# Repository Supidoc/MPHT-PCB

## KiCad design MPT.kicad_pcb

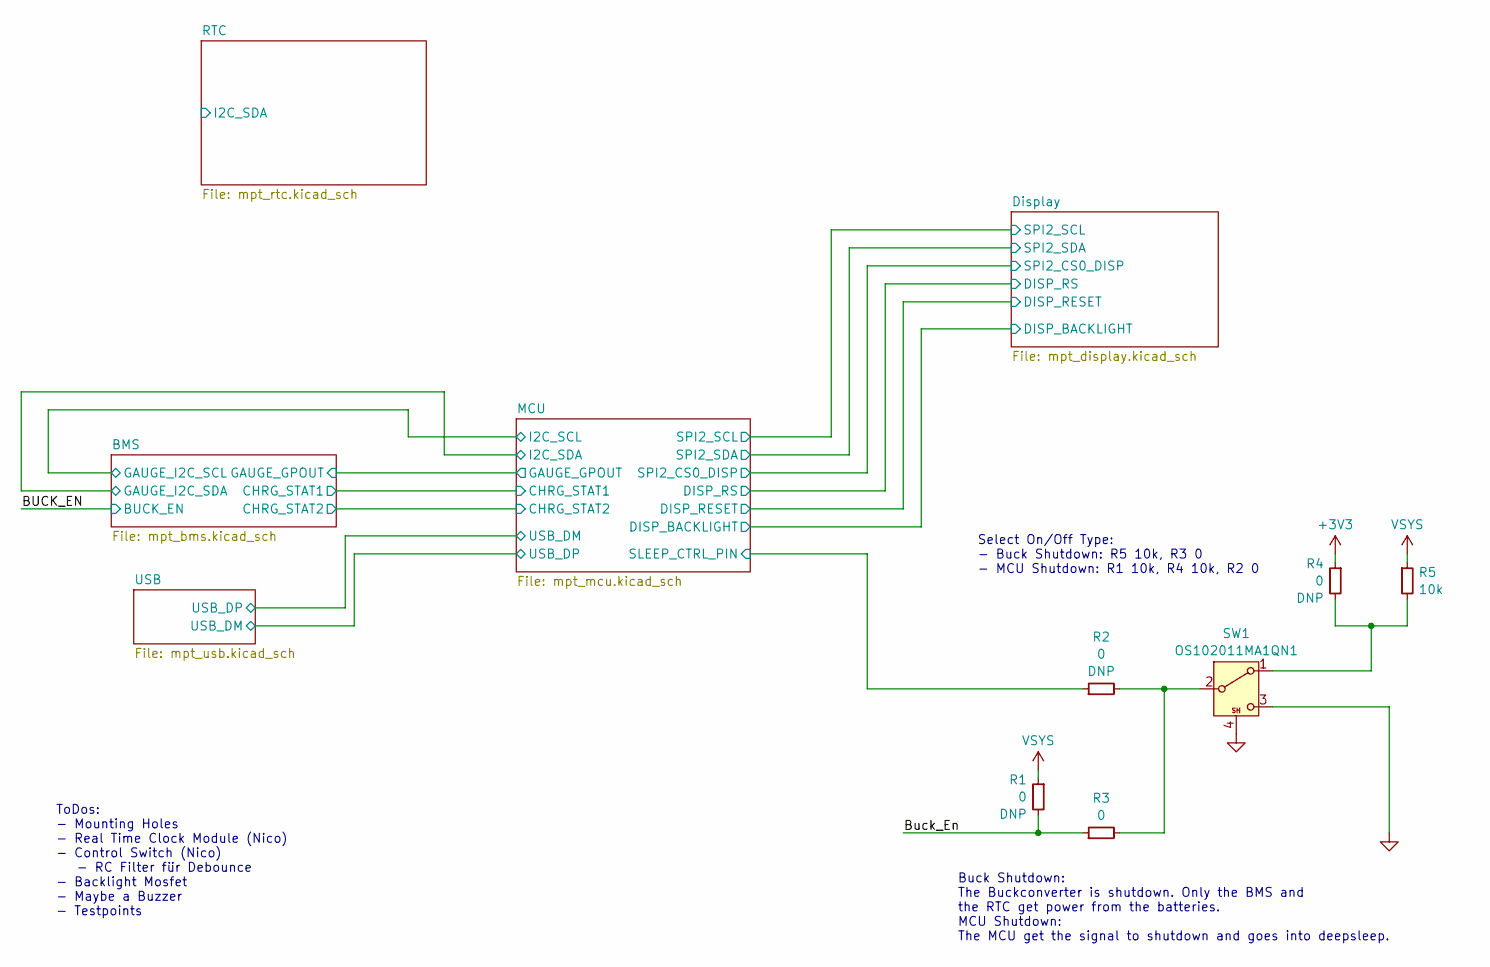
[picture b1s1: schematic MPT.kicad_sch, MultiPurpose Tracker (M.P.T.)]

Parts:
R1, R2, R4: 0; R_0603_DNP
R3: 0; R_0603; Rating 100mW; MFR# RC0603JR-070RL
R5: 10k; R_0603; Rating 125mW, 1%; MFR# RC0603FR-0710KL
SW1: OS102011MA1QN1; OS102011MA1QN1_CNK; Rating 100MA 12V Non-shorting; MFR# OS102011MA1QN1

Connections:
+3V3: R4.1; also elsewhere on the board
/Buck_En: R1.2, R3.1
/MCU/SLEEP_CTRL_PIN: R2.1; also elsewhere on the board
GND: SW1.3 (C), SW1.4 (SH); also elsewhere on the board
unnamed: R4.2, R5.2, SW1.1 (A)
unnamed: R2.2, R3.2, SW1.2 (B)
VSYS: R1.1, R5.1; also elsewhere on the board

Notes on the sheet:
Select On/Off Type: - Buck Shutdown: R5 10k, R3 0 - MCU Shutdown: R1 10k, R4 10k, R2 0
Buck Shutdown: The Buckconverter is shutdown. Only the BMS and the RTC get power from the batteries. MCU Shutdown: The MCU get the signal to shutdown and goes into deepsleep.
ToDos: - Mounting Holes - Real Time Clock Module (Nico) - Control Switch (Nico) - RC Filter für Debounce - Backlight Mosfet - Maybe a Buzzer - Testpoints

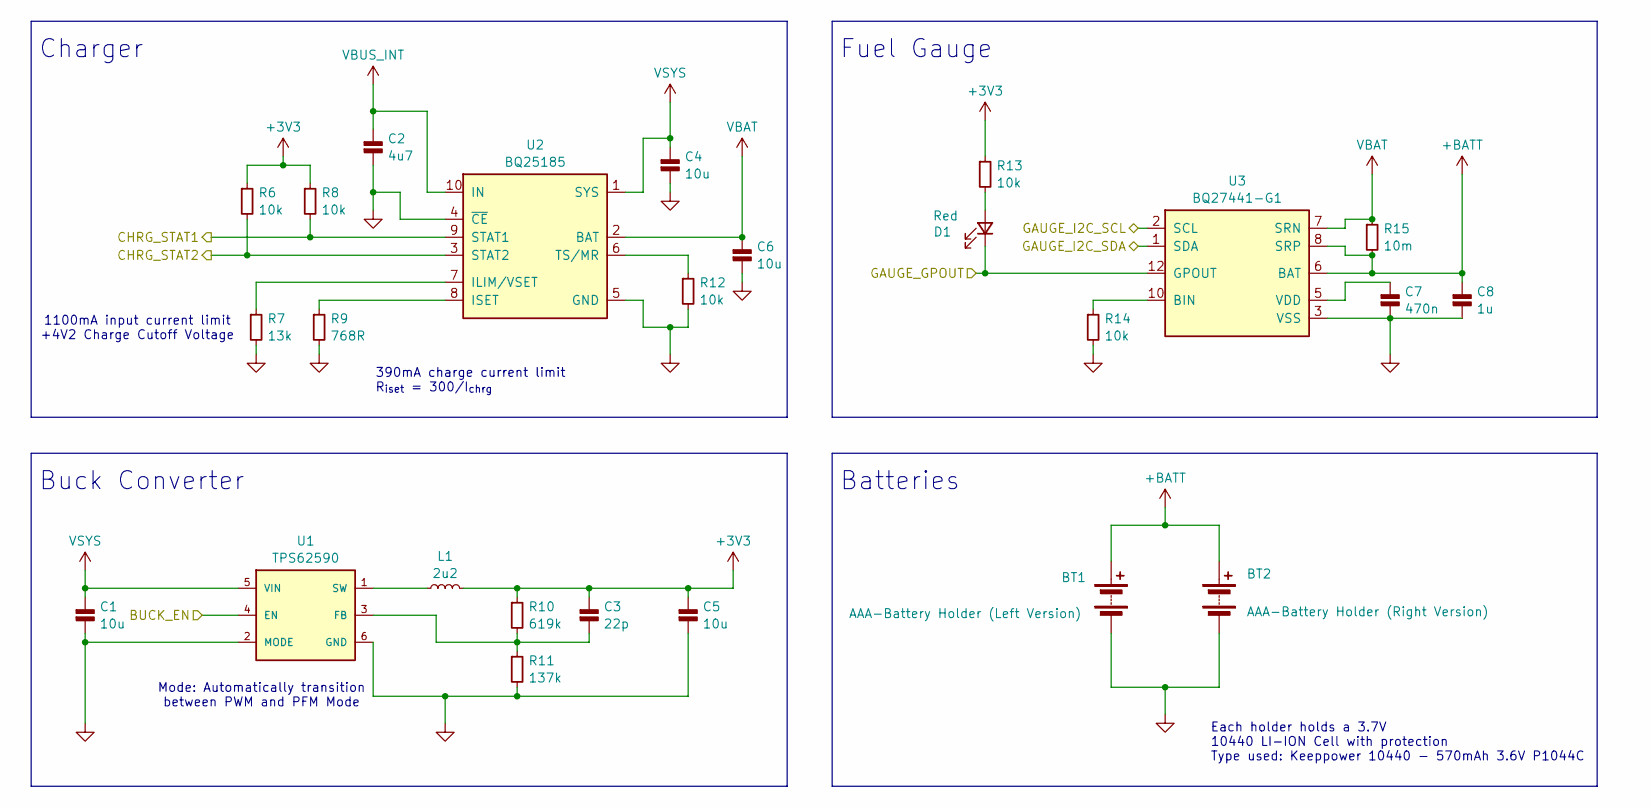
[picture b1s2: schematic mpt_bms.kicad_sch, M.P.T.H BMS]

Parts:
BT1: AAA-Battery Holder (Left Version); battery_holder_aaa_right_angle_left; MFR# 2466
BT2: AAA-Battery Holder (Right Version); battery_holder_aaa_right_angle_right; MFR# 2466
C1, C4, C5, C6: 10u; C_0603; Rating 10V 20%; MFR# CC0603MRX5R6BB106
C2: 4u7; C_0805; Rating 25V 10%; MFR# CC0805KKX7R8BB475
C3: 22p; C_0603; Rating 100V 5%; MFR# CC0603JPNPO0BN220
C7: 470n; C_0603; Rating 16V 10%; MFR# CC0603KRX7R7BB474
C8: 1u; C_0603; Rating 50V 10%; MFR# CC0603KRX7R9BB105
D1: Red; LED_0805_Right_Angle; Rating 20mA; MFR# LTST-S220KRKT
L1: 2u2; L_3.2mmx2.5mm; Rating 4A, 20%, 61mOhm; MFR# SRP3212-2R2M
R6, R8, R12, R13, R14: 10k; R_0603; Rating 125mW, 1%; MFR# RC0603FR-0710KL
R7: 13k; R_0603; Rating 125mW, 1%; MFR# RC0603FR-0713KL
R9: 768R; R_0603; Rating 125mW, 1%; MFR# RC0603FR-07768RL
R10: 619k; R_0603; Rating 125mW, 1%; MFR# RC0603FR-07619KL
R11: 137k; R_0603; Rating 125mW, 1%; MFR# RC0603FR-07137KL
R15: 10m; R_0603; Rating 0.5W, 1%; MFR# PA0603FRE570R01L
U1: TPS62590; WSON-6-1EP_2x2mm_P0.65mm; Rating 1A; MFR# TPS62590DRVR
U2: BQ25185; WSON-10-1EP_2.2x2mm_P0.4mm; Rating 1 Cell, 1 A; MFR# BQ25185DLHR
U3: BQ27441-G1; VSON-12-1EP_2.5_4mm_P0.4mm; MFR# BQ27441DRZR-G1A

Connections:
+3V3: C3.1, C5.1, L1.2, R6.1, R8.1, R10.1, R13.1; also elsewhere on the board
+BATT: BT1.1 (+), BT2.1 (+), C8.1, R15.2, U3.6 (BAT), U3.8 (SRP)
/BMS/CHRG_STAT1: R8.2, U2.9 (STAT1); also elsewhere on the board
/BMS/CHRG_STAT2: R6.2, U2.3 (STAT2); also elsewhere on the board
/BMS/GAUGE_GPOUT: D1.2 (K), U3.12 (GPOUT); also elsewhere on the board
/BMS/GAUGE_I2C_SCL: U3.2 (SCL); also elsewhere on the board
/BMS/GAUGE_I2C_SDA: U3.1 (SDA); also elsewhere on the board
/BUCK_EN: U1.4 (EN)
GND: BT1.2 (-), BT2.2 (-), C1.2, C2.2, C4.2, C5.2, C6.2, C7.2, C8.2, R7.2, R9.2, R11.2, R12.2, R14.2, U1.2 (MODE), U1.6 (GND), U1.7 (PAD), U2.0 (PAD), U2.4 (~CE), U2.5 (GND), U3.0 (PAD), U3.3 (VSS); also elsewhere on the board
unnamed: D1.1 (A), R13.2
unnamed: C3.2, R10.2, R11.1, U1.3 (FB)
unnamed: L1.1, U1.1 (SW)
unnamed: R7.1, U2.7 (ILIM/VSET)
unnamed: R9.1, U2.8 (ISET)
unnamed: R12.1, U2.6 (TS/MR)
unnamed: R14.1, U3.10 (BIN)
unnamed: C7.1, U3.5 (VDD)
VBAT: C6.1, R15.1, U2.2 (BAT), U3.7 (SRN)
VBUS_INT: C2.1, U2.10 (IN); also elsewhere on the board
VSYS: C1.1, C4.1, U1.5 (VIN), U2.1 (SYS); also elsewhere on the board

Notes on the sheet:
Charger
Buck Converter
390mA charge current limit R_{iset} = 300/I_{chrg}
Fuel Gauge
Batteries
Each holder holds a 3.7V 10440 LI-ION Cell with protection Type used: Keeppower 10440 - 570mAh 3.6V P1044C
Mode: Automatically transition between PWM and PFM Mode
1100mA input current limit +4V2 Charge Cutoff Voltage

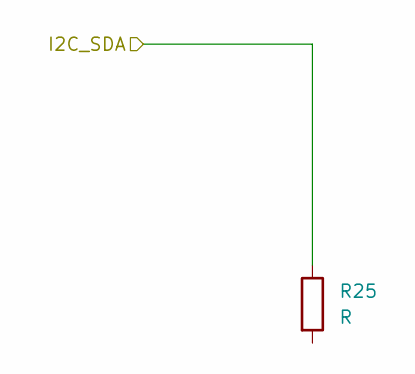
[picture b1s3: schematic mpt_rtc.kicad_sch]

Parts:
R25: R

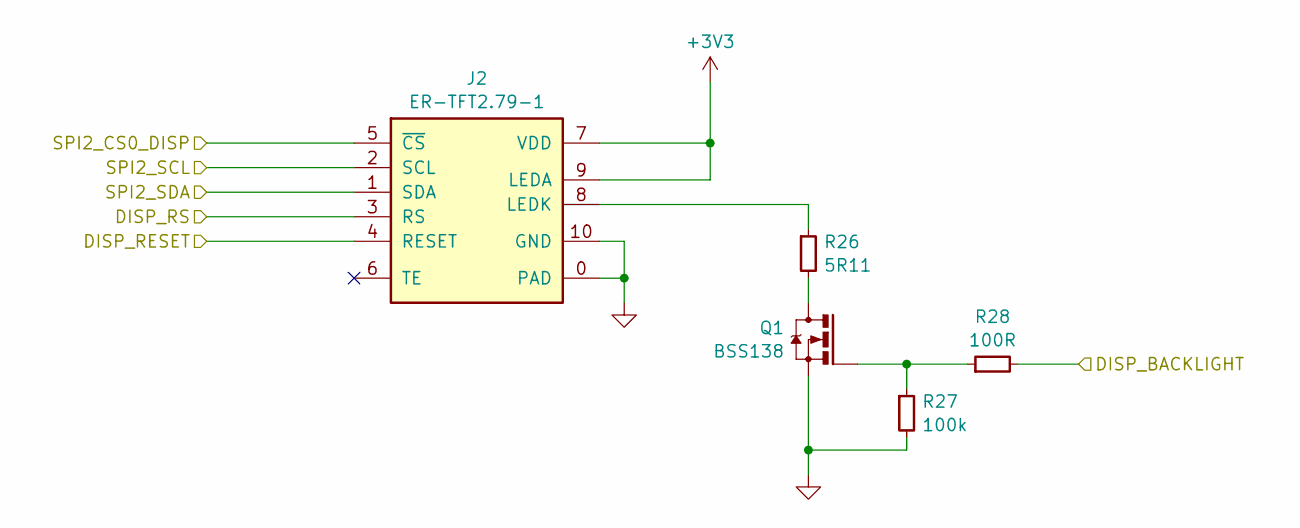
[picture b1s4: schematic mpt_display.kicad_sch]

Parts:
J2: ER-TFT2.79-1; Rating 2.79" IPS TFT LCD; MFR# ER-TFT2.79-1
Q1: BSS138; SOT-23; Rating 50 V 220mA; MFR# BSS138
R26: 5R11; R_0805; Rating 125mW, 1%; MFR# RC0805FR-075R11L
R27: 100k; R_0603; Rating 125mW, 1%; MFR# RC0603FR-07100KL
R28: 100R; R_0603; Rating 125mW, 1%; MFR# RC0603FR-07100RL

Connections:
+3V3: J2.7 (VDD), J2.9 (LEDA); also elsewhere on the board
/Display/DISP_BACKLIGHT: R28.2; also elsewhere on the board
/Display/DISP_RESET: J2.4 (RESET); also elsewhere on the board
/Display/DISP_RS: J2.3 (RS); also elsewhere on the board
/Display/SPI2_CS0_DISP: J2.5 (~CS); also elsewhere on the board
/Display/SPI2_SCL: J2.2 (SCL); also elsewhere on the board
/Display/SPI2_SDA: J2.1 (SDA); also elsewhere on the board
GND: J2.0 (PAD), J2.10 (GND), Q1.2 (S), R27.2; also elsewhere on the board
unnamed: J2.8 (LEDK), R26.1
unnamed: Q1.3 (D), R26.2
unnamed: Q1.1 (G), R27.1, R28.1

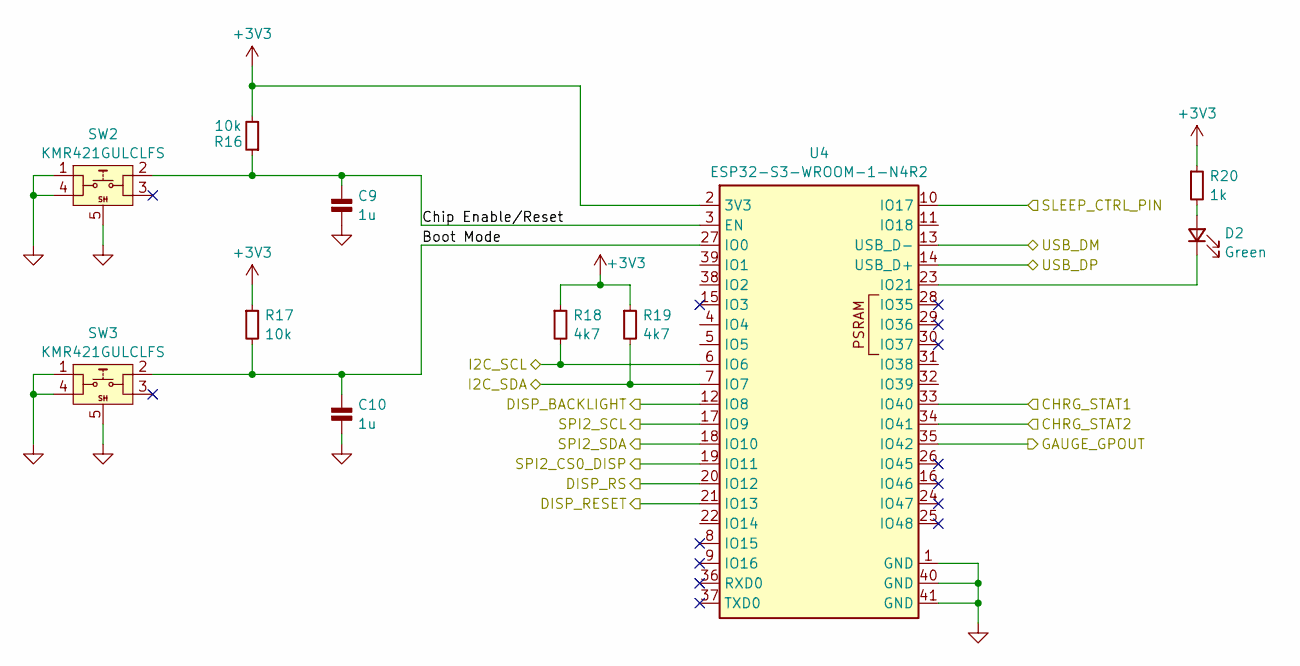
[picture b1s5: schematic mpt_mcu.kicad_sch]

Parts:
C9, C10: 1u; C_0603; Rating 50V 10%; MFR# CC0603KRX7R9BB105
D2: Green; D_0603; Rating 2v1 20mA 569nm; MFR# LTST-C190GKT
R16, R17: 10k; R_0603; Rating 125mW, 1%; MFR# RC0603FR-0710KL
R18, R19: 4k7; R_0603; Rating 100mW, 1%; MFR# RC0603FR-074K7L
R20: 1k; R_0603; Rating 125mW, 1%; MFR# RC0603FR-071KL
SW2, SW3: KMR421GULCLFS; Rating 1VA; MFR# KMR421GULCLFS
U4: ESP32-S3-WROOM-1-N4R2; ESP32_S3_WROOM_1; Rating 4 MB Flash, 2 MB PSRAM; MFR# ESP32-S3-WROOM-1-N4R2

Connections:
+3V3: R16.2, R17.1, R18.1, R19.1, R20.1, U4.2 (3V3); also elsewhere on the board
/BMS/CHRG_STAT1: U4.33 (IO40); also elsewhere on the board
/BMS/CHRG_STAT2: U4.34 (IO41); also elsewhere on the board
/BMS/GAUGE_GPOUT: U4.35 (IO42); also elsewhere on the board
/BMS/GAUGE_I2C_SCL: R18.2, U4.6 (IO6); also elsewhere on the board
/BMS/GAUGE_I2C_SDA: R19.2, U4.7 (IO7); also elsewhere on the board
/Display/DISP_BACKLIGHT: U4.12 (IO8); also elsewhere on the board
/Display/DISP_RESET: U4.21 (IO13); also elsewhere on the board
/Display/DISP_RS: U4.20 (IO12); also elsewhere on the board
/Display/SPI2_CS0_DISP: U4.19 (IO11); also elsewhere on the board
/Display/SPI2_SCL: U4.17 (IO9); also elsewhere on the board
/Display/SPI2_SDA: U4.18 (IO10); also elsewhere on the board
/MCU/Boot Mode: C10.1, R17.2, SW3.2, U4.27 (IO0)
/MCU/Chip Enable/Reset: C9.1, R16.1, SW2.2, U4.3 (EN)
/MCU/SLEEP_CTRL_PIN: U4.10 (IO17); also elsewhere on the board
/MCU/USB_DM: U4.13 (USB_D-); also elsewhere on the board
/MCU/USB_DP: U4.14 (USB_D+); also elsewhere on the board
GND: C9.2, C10.2, SW2.1, SW2.4 (3), SW2.5 (SH), SW3.1, SW3.4 (3), SW3.5 (SH), U4.1 (GND), U4.40 (GND), U4.41 (GND); also elsewhere on the board
unnamed: D2.1 (A), R20.2
unnamed: D2.2 (K), U4.23 (IO21)

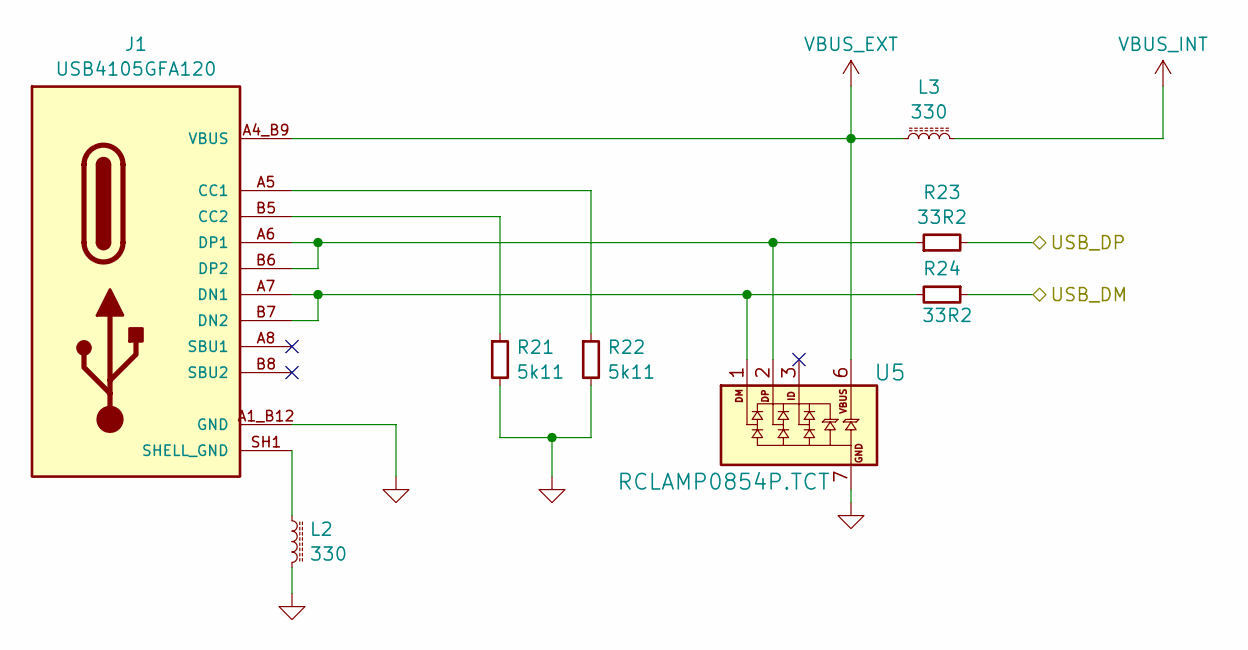
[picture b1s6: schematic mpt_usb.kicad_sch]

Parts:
J1: USB4105GFA120; GCT_USB4105GFA120; Rating 16 Pin; MFR# USB4105-GF-A-120
L2, L3: 330; L_0603; Rating 330 Ohms @ 100 MHz 1.7A 80mOhm; MFR# MPZ1608S331ATA00
R21, R22: 5k11; R_0603; Rating 125mW, 1%; MFR# RC0603FR-075K11L
R23, R24: 33R2; R_0603; Rating 125mW, 1%; MFR# RC0603FR-0733R2L
U5: RCLAMP0854P.TCT; UFDFN06_1P6X1P6; Rating 5.5VWM 30VC; MFR# RCLAMP0854P.TCT

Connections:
/MCU/USB_DM: R23.2; also elsewhere on the board
/MCU/USB_DP: R24.1; also elsewhere on the board
GND: J1.A1_B12 (GND), J1.B1_A12 (GND), L2.2, R21.2, R22.2, U5.7 (GND); also elsewhere on the board
unnamed: J1.A5 (CC1), R22.1
unnamed: J1.B5 (CC2), R21.1
unnamed: J1.A7 (DN1), J1.B7 (DN2), R24.2, U5.1 (DM)
unnamed: J1.A6 (DP1), J1.B6 (DP2), R23.1, U5.2 (DP)
SHELL_GND: J1.SH1 (SHELL_GND), J1.SH2 (SHELL_GND), J1.SH3 (SHELL_GND), J1.SH4 (SHELL_GND), L2.1
VBUS_EXT: J1.A4_B9 (VBUS), J1.B4_A9 (VBUS), L3.1, U5.6 (VBUS)
VBUS_INT: L3.2; also elsewhere on the board

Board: 2 copper layers, 55 parts (0 on the bottom side), 44 nets, no tracks yet.

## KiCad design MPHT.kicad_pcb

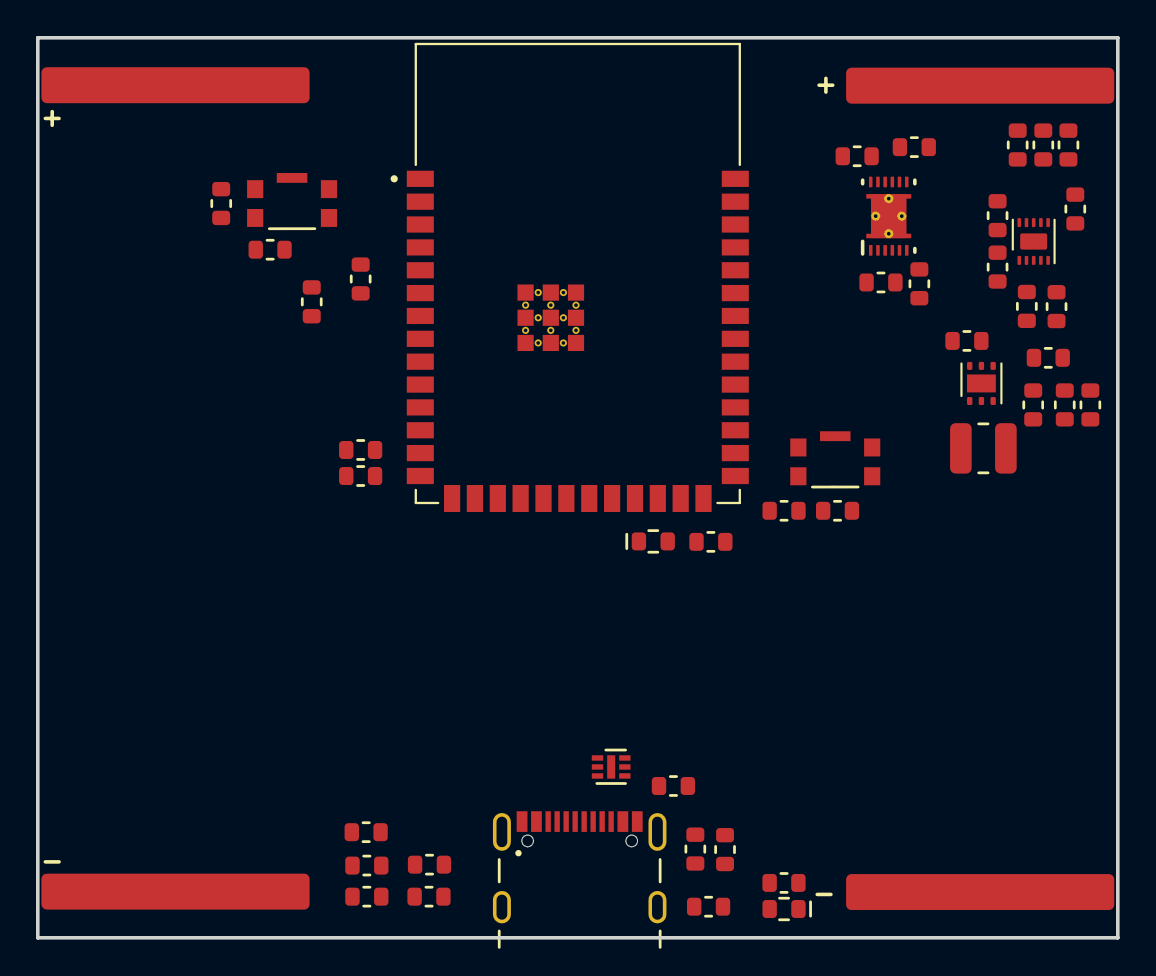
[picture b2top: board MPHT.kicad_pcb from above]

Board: 2 copper layers, 60.0 x 50.0 mm, 49 parts (0 on the bottom side), 35 nets, no tracks yet.

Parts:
BT3: AAA-Battery Holder (Left Version); battery_holder_aaa_right_angle_left
BT4: AAA-Battery Holder (Right Version); battery_holder_aaa_right_angle_right
C1, C2, C3: 1u; C_0603
C4, C5, C7, C9: 10u; C_0603
C6: 22p; C_0603
C8: 470n; C_0603
C109: 4u7; C_0603
D1: Orange; D_0603
D104: Green; D_0603
J101: USB4105GFA120; GCT_USB4105GFA120
L2: 2u2; L_3.2mmx2.5mm
L102, L103: 330; L_0603
R1, R6, R11, R13, R17, R18, R19, R107: 10k; R_0603
R2, R3: 4k7; R_0603
R4, R8, R9: 0; R_0603_DNP
R5: 0; R_0603
R12: 13k; R_0603
R14: 604R; R_0603
R15: 619k; R_0603
R16: 137k; R_0603
R20: 10m; R_0603
R101, R102: 5k1; R_0603
R103, R104: 33; R_0603
R115: 1k; R_0603
SW101, SW102: KMR421GULCLFS
U1: ESP32-S3-WROOM-1-N4R2; ESP32_S3_WROOM_1
U4: TPS62590; WSON-6-1EP_2x2mm_P0.65mm
U5: BQ25185; WSON-10-1EP_2.2x2mm_P0.4mm
U6: BQ27441-G1; VSON-12-1EP_2.5_4mm_P0.4mm
U101: RCLAMP0854P.TCT; UFDFN06_1P6X1P6

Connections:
+3V3: C6.1, C7.1, L2.2, R1.1, R2.1, R3.1, R8.1, R11.1, R13.1, R15.1, R18.1, R107.1, R115.1, U1.2 (3V3)
+BATT: C3.1, R20.2, U6.6 (BAT), U6.8 (SRP)
/BMS/CHRG_STAT1: R13.2, U1.33 (IO40), U5.9 (STAT1)
/BMS/CHRG_STAT2: R11.2, U1.34 (IO41), U5.3 (STAT2)
/BMS/GAUGE_GPOUT: D1.2 (K), U1.35 (IO42), U6.12 (GPOUT)
/BMS/GAUGE_I2C_SCL: R2.2, U1.6 (IO6), U6.2 (SCL)
/BMS/GAUGE_I2C_SDA: R3.2, U1.7 (IO7), U6.1 (SDA)
/Buck_En: R5.1, R9.2, U4.4 (EN)
/MCU/Boot Mode: C2.1, R107.2, SW101.2, U1.27 (IO0)
/MCU/Chip Enable/Reset: C1.1, R1.2, SW102.2, U1.3 (EN)
/MCU/SLEEP_CTRL_PIN: R4.1, U1.10 (IO17)
/MCU/USB_DM: R103.2, U1.13 (USB_D-)
/MCU/USB_DP: R104.2, U1.14 (USB_D+)
GND: C1.2, C2.2, C3.2, C4.2, C5.2, C7.2, C8.2, C9.2, C109.2, J101.A1_B12 (GND), J101.B1_A12 (GND), L102.2, R12.2, R14.2, R16.2, R17.2, R19.2, R101.2, R102.2, SW101.1, SW101.4 (3), SW101.5 (SH), SW102.1, SW102.4 (3), SW102.5 (SH), U1.1 (GND), U1.40 (GND), U4.2 (MODE), U4.6 (GND), U5.4 (~CE), U5.5 (GND), U6.3 (VSS), U101.7 (GND)
unnamed: D1.1 (A), R18.2
unnamed: D104.1 (A), R115.2
unnamed: D104.2 (K), U1.23 (IO21)
unnamed: J101.A5 (CC1), R102.1
unnamed: J101.B5 (CC2), R101.1
unnamed: J101.A7 (DN1), J101.B7 (DN2), R104.1, U101.1 (DM)
unnamed: J101.A6 (DP1), J101.B6 (DP2), R103.1, U101.2 (DP)
unnamed: R6.2, R8.2
unnamed: R4.2, R5.2
unnamed: C6.2, R15.2, R16.1, U4.3 (FB)
unnamed: L2.1, U4.1 (SW)
unnamed: R12.1, U5.7 (ILIM/VSET)
unnamed: R14.1, U5.8 (ISET)
unnamed: R17.1, U5.6 (TS/MR)
unnamed: R19.1, U6.10 (BIN)
unnamed: C8.1, U6.5 (VDD)
SHELL_GND: J101.SH1 (SHELL_GND), J101.SH2 (SHELL_GND), J101.SH3 (SHELL_GND), J101.SH4 (SHELL_GND), L102.1
VBAT: C9.1, R20.1, U5.2 (BAT), U6.7 (SRN)
VBUS_EXT: J101.A4_B9 (VBUS), J101.B4_A9 (VBUS), L103.1, U101.6 (VBUS)
VBUS_INT: C109.1, L103.2, U5.10 (IN)
VSYS: C4.1, C5.1, R6.1, R9.1, U4.5 (VIN), U5.1 (SYS)
